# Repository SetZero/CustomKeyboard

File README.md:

# Custom Keyboard

This is a custom Keyboard layout with macro keys

## Layout File

See on [keyboard-layout-editor.com](http://www.keyboard-layout-editor.com/##@@_y:0.5%3B&=Esc&_x:1%3B&=F1&=F2&=F3&=F4&_x:0.5%3B&=F5&=F6&=F7&=F8&_x:0.5%3B&=F9&=F10&=F11&=F12&=PrtSc&=Scroll%20Lock&=Pause%0ABreak%3B&@=%C2%AC%0A%60&=!%0A1&=%22%0A2&=%C2%A3%0A3&=$%0A4&=%25%0A5&=%5E%0A6&=%2F&%0A7&=*%0A8&=(%0A9&=)%0A0&=%2F_%0A-&=+%0A%2F=&_w:2%3B&=Backspace&=Insert&=Home&=PgUp%3B&@_w:1.5%3B&=Tab&=Q&=W&=E&=R&=T&=Y&=U&=I&=O&=P&=%7B%0A%5B&=%7D%0A%5D&_x:0.25&w:1.25&h:2&w2:1.5&h2:1&x2:-0.25%3B&=Enter&=Delete&=End&=PgDn%3B&@_w:1.75%3B&=Caps%20Lock&=A&=S&=D&=F&=G&=H&=J&=K&=L&=%2F:%0A%2F%3B&=%2F@%0A'&=~%0A%23&_x:1.25%3B&=M1&=M2&=M3%3B&@_w:1.25%3B&=Shift&=%7C%0A%5C&=Z&=X&=C&=V&=B&=N&=M&=%3C%0A,&=%3E%0A.&=%3F%0A%2F%2F&_w:2.75%3B&=Shift&_x:1%3B&=%E2%86%91%3B&@_w:1.25%3B&=Ctrl&_w:1.25%3B&=Win&_w:1.25%3B&=Alt&_a:7&w:6.25%3B&=&_a:4&w:1.25%3B&=AltGr&_w:1.25%3B&=Win&_w:1.25%3B&=Menu&_w:1.25%3B&=Ctrl&=%E2%86%90&=%E2%86%93&=%E2%86%92)

Generated by [kb.xyz.is](https://kb.xyz.is/)

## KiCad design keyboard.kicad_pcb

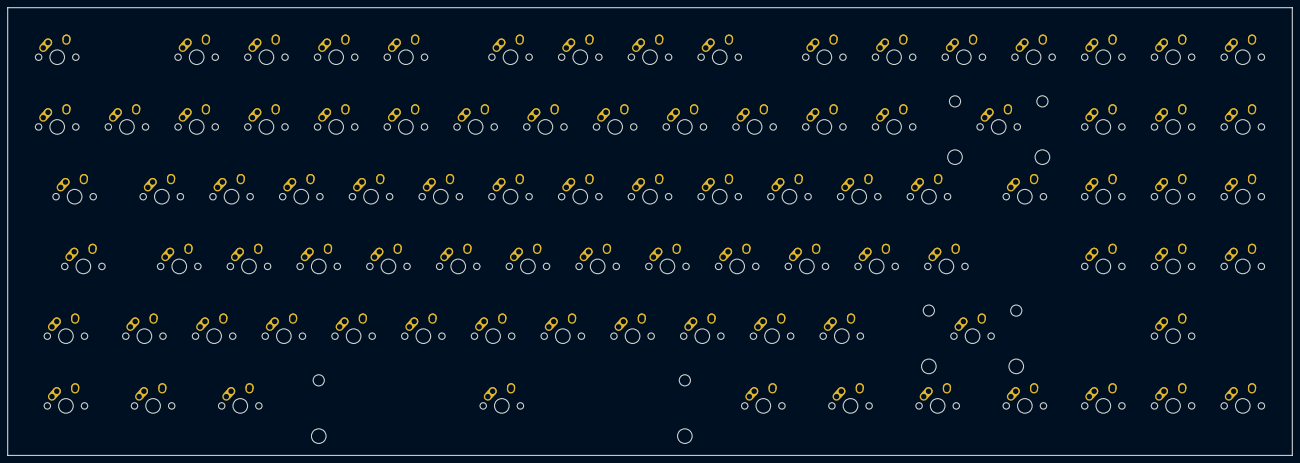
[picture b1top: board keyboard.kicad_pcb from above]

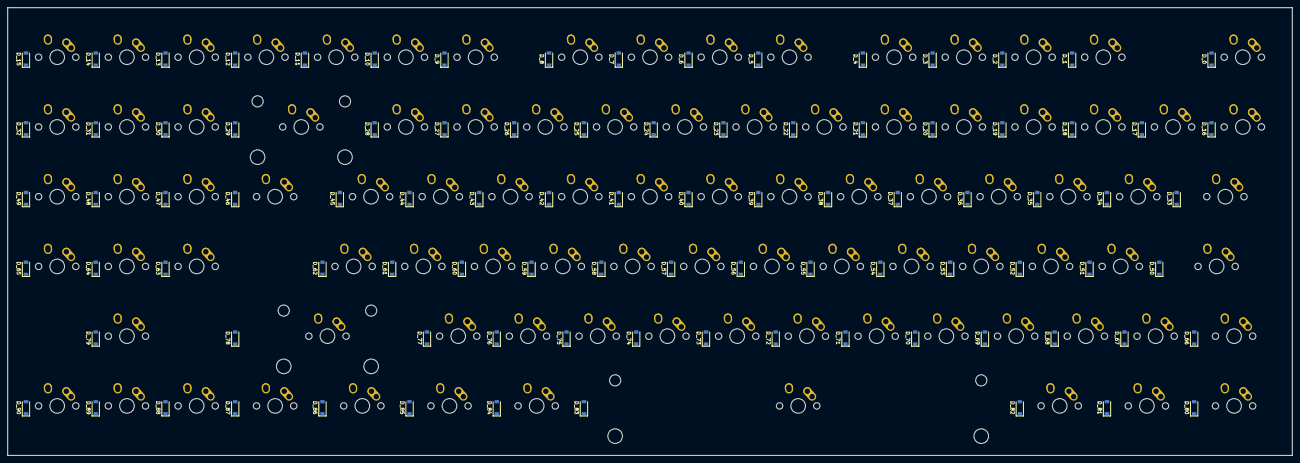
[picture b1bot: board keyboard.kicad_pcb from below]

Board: 2 copper layers, 350.9 x 122.3 mm, 182 parts (91 on the bottom side), 115 nets, no tracks yet.

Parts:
D_0, D_1, D_2, D_3, D_4, D_5, D_6, D_7, D_8, D_9, D_10, D_11, D_12, D_13, D_14, D_15, D_16, D_17, D_18, D_19, D_20, D_21, D_22, D_23, D_24, D_25, D_26, D_27, D_28, D_29, D_30, D_31, D_32, D_33, D_34, D_35, D_36, D_37, D_38, D_39, D_40, D_41, D_42, D_43, D_44, D_45, D_46, D_47, D_48, D_49, D_50, D_51, D_52, D_53, D_54, D_55, D_56, D_57, D_58, D_59, D_60, D_61, D_62, D_63, D_64, D_65, D_66, D_67, D_68, D_69, D_70, D_71, D_72, D_73, D_74, D_75, D_76, D_77, D_78, D_79, D_80, D_81, D_82, D_83, D_84, D_85, D_86, D_87, D_88, D_89, D_90: D; D_SOD-123
K_0, K_1, K_2, K_3, K_4, K_5, K_6, K_7, K_8, K_9, K_10, K_11, K_12, K_13, K_14, K_15, K_16, K_17, K_18, K_19, K_20, K_21, K_22, K_23, K_24, K_25, K_26, K_27, K_28, K_30, K_31, K_32, K_34, K_35, K_36, K_37, K_38, K_39, K_40, K_41, K_42, K_43, K_44, K_45, K_47, K_48, K_49, K_51, K_52, K_53, K_54, K_55, K_56, K_57, K_58, K_59, K_60, K_61, K_62, K_63, K_64, K_65, K_67, K_68, K_69, K_70, K_71, K_72, K_73, K_74, K_75, K_76, K_77, K_79, K_88, K_89, K_90: KEYSW; MX-1U-NoLED
K_29: KEYSW; MX-2U-NoLED
K_33: KEYSW; MX-1.5U-NoLED
K_46, K_66, K_80, K_81, K_82, K_84, K_85, K_86, K_87: KEYSW; MX-1.25U-NoLED
K_50: KEYSW; MX-1.75U-NoLED
K_78: KEYSW; MX-2.75U-NoLED
K_83: KEYSW; MX-6.25U-NoLED

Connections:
unnamed: D_0.2, K_0.2
unnamed: D_1.2, K_1.2
unnamed: D_2.2, K_2.2
unnamed: D_3.2, K_3.2
unnamed: D_4.2, K_4.2
unnamed: D_5.2, K_5.2
unnamed: D_6.2, K_6.2
unnamed: D_7.2, K_7.2
unnamed: D_8.2, K_8.2
unnamed: D_9.2, K_9.2
unnamed: D_10.2, K_10.2
unnamed: D_11.2, K_11.2
unnamed: D_12.2, K_12.2
unnamed: D_13.2, K_13.2
unnamed: D_14.2, K_14.2
unnamed: D_15.2, K_15.2
unnamed: D_16.2, K_16.2
unnamed: D_17.2, K_17.2
unnamed: D_18.2, K_18.2
unnamed: D_19.2, K_19.2
unnamed: D_20.2, K_20.2
unnamed: D_21.2, K_21.2
unnamed: D_22.2, K_22.2
unnamed: D_23.2, K_23.2
unnamed: D_24.2, K_24.2
unnamed: D_25.2, K_25.2
unnamed: D_26.2, K_26.2
unnamed: D_27.2, K_27.2
unnamed: D_28.2, K_28.2
unnamed: D_29.2, K_29.2
unnamed: D_30.2, K_30.2
unnamed: D_31.2, K_31.2
unnamed: D_32.2, K_32.2
unnamed: D_33.2, K_33.2
unnamed: D_34.2, K_34.2
unnamed: D_35.2, K_35.2
unnamed: D_36.2, K_36.2
unnamed: D_37.2, K_37.2
unnamed: D_38.2, K_38.2
unnamed: D_39.2, K_39.2
unnamed: D_40.2, K_40.2
unnamed: D_41.2, K_41.2
unnamed: D_42.2, K_42.2
unnamed: D_43.2, K_43.2
unnamed: D_44.2, K_44.2
unnamed: D_45.2, K_45.2
unnamed: D_46.2, K_46.2
unnamed: D_47.2, K_47.2
unnamed: D_48.2, K_48.2
unnamed: D_49.2, K_49.2
unnamed: D_50.2, K_50.2
unnamed: D_51.2, K_51.2
unnamed: D_52.2, K_52.2
unnamed: D_53.2, K_53.2
unnamed: D_54.2, K_54.2
unnamed: D_55.2, K_55.2
unnamed: D_56.2, K_56.2
unnamed: D_57.2, K_57.2
unnamed: D_58.2, K_58.2
unnamed: D_59.2, K_59.2
unnamed: D_60.2, K_60.2
unnamed: D_61.2, K_61.2
unnamed: D_62.2, K_62.2
unnamed: D_63.2, K_63.2
unnamed: D_64.2, K_64.2
unnamed: D_65.2, K_65.2
unnamed: D_66.2, K_66.2
unnamed: D_67.2, K_67.2
unnamed: D_68.2, K_68.2
unnamed: D_69.2, K_69.2
unnamed: D_70.2, K_70.2
unnamed: D_71.2, K_71.2
unnamed: D_72.2, K_72.2
unnamed: D_73.2, K_73.2
unnamed: D_74.2, K_74.2
unnamed: D_75.2, K_75.2
unnamed: D_76.2, K_76.2
unnamed: D_77.2, K_77.2
unnamed: D_78.2, K_78.2
unnamed: D_79.2, K_79.2
unnamed: D_80.2, K_80.2
unnamed: D_81.2, K_81.2
unnamed: D_82.2, K_82.2
unnamed: D_83.2, K_83.2
unnamed: D_84.2, K_84.2
unnamed: D_85.2, K_85.2
unnamed: D_86.2, K_86.2
unnamed: D_87.2, K_87.2
unnamed: D_88.2, K_88.2
unnamed: D_89.2, K_89.2
unnamed: D_90.2, K_90.2
col0: K_0.1, K_16.1, K_33.1, K_50.1, K_66.1, K_80.1
col1: K_17.1, K_67.1, K_81.1
col2: K_1.1, K_18.1, K_34.1, K_51.1, K_68.1
col3: K_2.1, K_19.1, K_35.1, K_52.1, K_69.1, K_82.1
col4: K_3.1, K_20.1, K_36.1, K_53.1, K_70.1
col5: K_4.1, K_21.1, K_37.1, K_54.1, K_71.1
col6: K_22.1, K_38.1, K_55.1, K_72.1, K_83.1
col7: K_5.1, K_23.1, K_39.1, K_56.1, K_73.1
col8: K_6.1, K_24.1, K_40.1, K_57.1, K_74.1
col9: K_7.1, K_25.1, K_41.1, K_58.1, K_75.1
col10: K_8.1, K_26.1, K_42.1, K_59.1, K_76.1, K_84.1
col11: K_9.1, K_27.1, K_43.1, K_60.1, K_77.1, K_85.1
col12: K_10.1, K_28.1, K_44.1, K_61.1
col13: K_11.1, K_45.1, K_62.1, K_78.1, K_86.1
col14: K_12.1, K_29.1, K_46.1, K_87.1
col15: K_13.1, K_30.1, K_47.1, K_63.1, K_88.1
col16: K_14.1, K_31.1, K_48.1, K_64.1, K_79.1, K_89.1
col17: K_15.1, K_32.1, K_49.1, K_65.1, K_90.1
row0: D_0.1, D_1.1, D_2.1, D_3.1, D_4.1, D_5.1, D_6.1, D_7.1, D_8.1, D_9.1, D_10.1, D_11.1, D_12.1, D_13.1, D_14.1, D_15.1
row1: D_16.1, D_17.1, D_18.1, D_19.1, D_20.1, D_21.1, D_22.1, D_23.1, D_24.1, D_25.1, D_26.1, D_27.1, D_28.1, D_29.1, D_30.1, D_31.1, D_32.1
row2: D_33.1, D_34.1, D_35.1, D_36.1, D_37.1, D_38.1, D_39.1, D_40.1, D_41.1, D_42.1, D_43.1, D_44.1, D_45.1, D_47.1, D_48.1, D_49.1
row3: D_46.1, D_50.1, D_51.1, D_52.1, D_53.1, D_54.1, D_55.1, D_56.1, D_57.1, D_58.1, D_59.1, D_60.1, D_61.1, D_62.1, D_63.1, D_64.1, D_65.1
row4: D_66.1, D_67.1, D_68.1, D_69.1, D_70.1, D_71.1, D_72.1, D_73.1, D_74.1, D_75.1, D_76.1, D_77.1, D_78.1, D_79.1
row5: D_80.1, D_81.1, D_82.1, D_83.1, D_84.1, D_85.1, D_86.1, D_87.1, D_88.1, D_89.1, D_90.1

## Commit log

2023-01-28 Added: + Libraries for Symbols and Footprints + STM32L412 Symbol and Footprint + Hierachical sheets: key_matrix.kicad_sch, supply.kicad_sch
2023-01-28 Add initial connector pin assignment
2023-01-28 Add Keyboard Layout description to readme
2023-01-28 added NUF2030 footprint and symbol
2023-01-28 Add wiring for NUF2030
2023-01-29 Update Layout + Add CubeMX file
2023-02-01 Supply: - Added voltage regulator - appended calculations for L and Voltage divider - Added USB-C connector symbol and connected D+/D- lines
2023-02-01 Added CC1 / CC2
2023-02-01 added new stm uc
2023-02-01 Added wiring for new mcu
